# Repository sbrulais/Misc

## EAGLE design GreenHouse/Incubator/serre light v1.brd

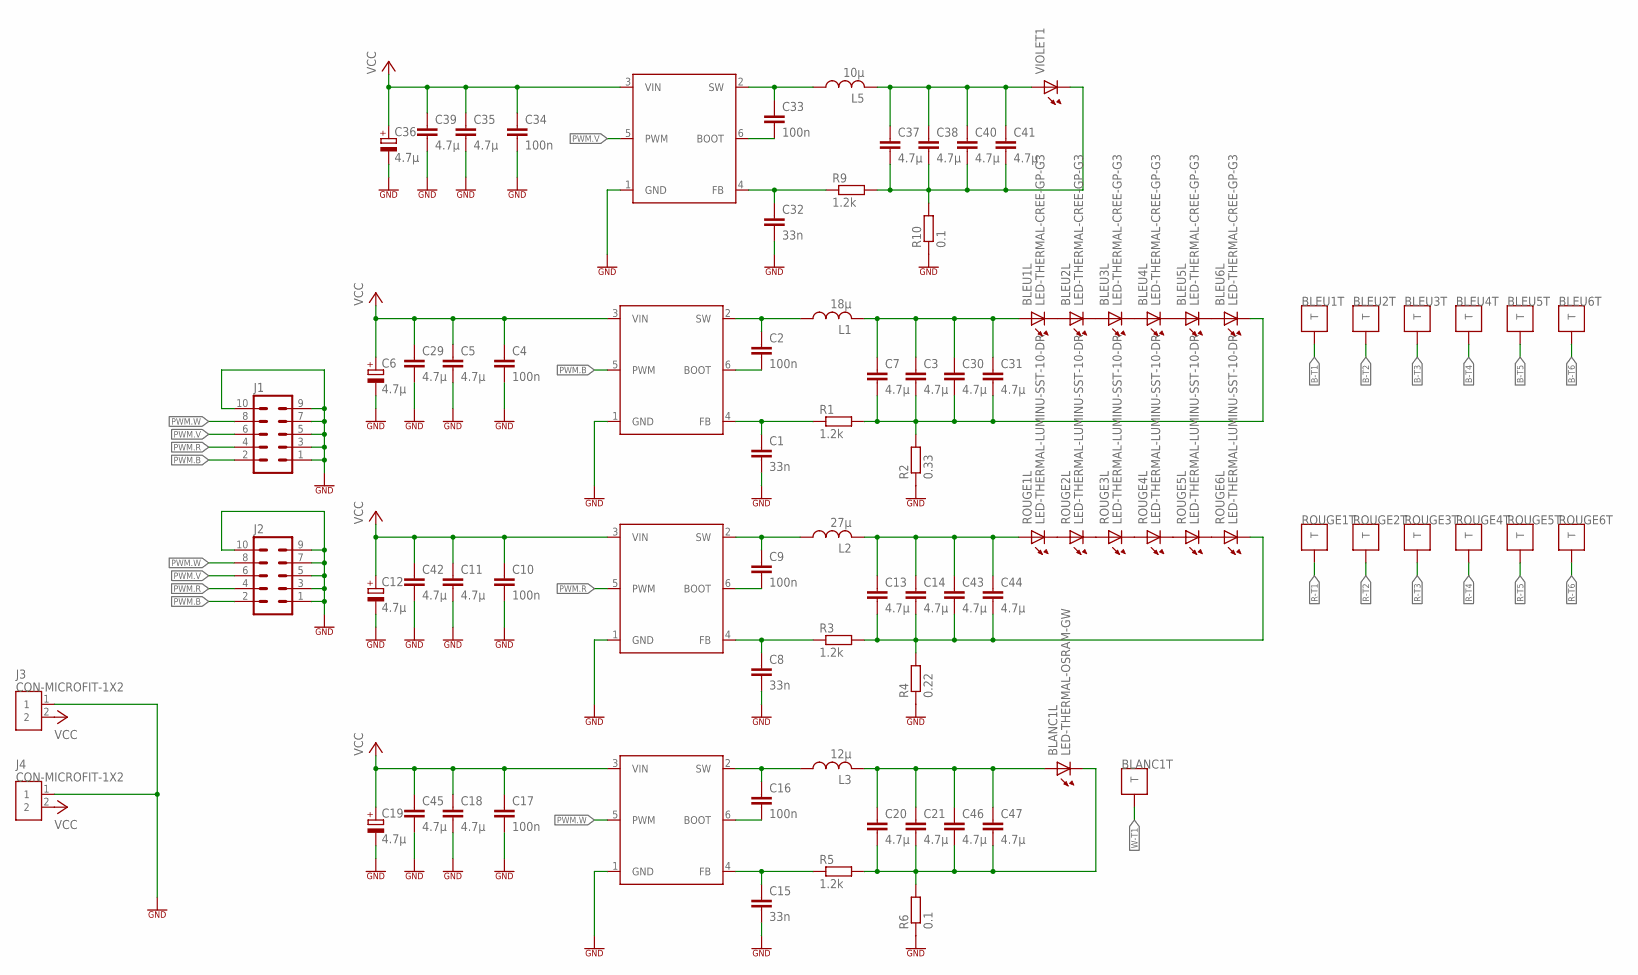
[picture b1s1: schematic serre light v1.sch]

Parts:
BLANC1: LED-THERMAL-OSRAM-GW; LED-OSRAM-GW
BLEU1, BLEU2, BLEU3, BLEU4, BLEU5, BLEU6: LED-THERMAL-CREE-GP-G3; LED-CREE-GP-G3
C1, C8, C15, C32: 33n; C0603
C2, C9, C16, C33: 100n; C0603
C3, C5, C7, C11, C13, C14, C18, C20, C21, C29, C30, C31, C35, C37, C38, C39, C40, C41, C42, C43, C44, C45, C46, C47: 4.7µ; C1210
C4, C10, C17, C34: 100n; C0805
C6, C12, C19, C36: 4.7µ; CAP-TANT-B
IC1, IC2, IC3, IC5: TPS54201; SOT23-6
J1, J2: ML10
J3, J4: CON-MICROFIT-1X2; MICROFIT-1X2
L1: 18µ; L-COILCRAFT-MSS1038; FARNELL 2288206
L2: 27µ; L-COILCRAFT-MSS1038; FARNELL 2288208
L3: 12µ; L-COILCRAFT-MSS1038; FARNELL 2288210
L5: 10µ; L-COILCRAFT-MSS1038; FARNELL 2288225
R1, R3, R5, R9: 1.2k; R0805
R2: 0.33; R1206; FARNELL 2328126
R4: 0.22; R1206; FARNELL 2824735
R6: 0.1; R1206; FARNELL 1100335
R10: 0.1; R1206; FARNELL 1099913
ROUGE1, ROUGE2, ROUGE3, ROUGE4, ROUGE5, ROUGE6: LED-THERMAL-LUMINU-SST-10-DR; LED-LUMINU-SST-10-DR
VIOLET1: LED-LUXEON-UV-U2

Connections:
B-T1: BLEU1.THERMAL (T)
B-T2: BLEU2.THERMAL (T)
B-T3: BLEU3.THERMAL (T)
B-T4: BLEU4.THERMAL (T)
B-T5: BLEU5.THERMAL (T)
B-T6: BLEU6.THERMAL (T)
GND: C1.2, C4.2, C5.2, C6.-, C8.2, C10.2, C11.2, C12.-, C15.2, C17.2, C18.2, C19.-, C29.2, C32.2, C34.2, C35.2, C36.-, C39.2, C42.2, C45.2, IC1.1 (GND), IC2.1 (GND), IC3.1 (GND), IC5.1 (GND), J1.1, J1.3, J1.5, J1.7, J1.9, J1.10, J2.1, J2.3, J2.5, J2.7, J2.9, J2.10, J3.1, J4.1, R2.1, R4.1, R6.1, R10.1
unnamed: BLEU2.C, BLEU3.A
unnamed: BLEU1.C, BLEU2.A
unnamed: BLEU3.C, BLEU4.A
unnamed: BLEU4.C, BLEU5.A
unnamed: ROUGE1.C, ROUGE2.A
unnamed: ROUGE2.C, ROUGE3.A
unnamed: ROUGE3.C, ROUGE4.A
unnamed: ROUGE5.C, ROUGE6.A
unnamed: ROUGE4.C, ROUGE5.A
unnamed: BLEU5.C, BLEU6.A
unnamed: C1.1, IC1.4 (FB), R1.1
unnamed: C2.1, IC1.2 (SW), L1.1
unnamed: C2.2, IC1.6 (BOOT)
unnamed: BLEU6.C, C3.2, C7.2, C30.2, C31.2, R1.2, R2.2
unnamed: C8.1, IC2.4 (FB), R3.1
unnamed: BLEU1.A, C3.1, C7.1, C30.1, C31.1, L1.2
unnamed: C9.1, IC2.2 (SW), L2.1
unnamed: C9.2, IC2.6 (BOOT)
unnamed: C13.2, C14.2, C43.2, C44.2, R3.2, R4.2, ROUGE6.C
unnamed: C13.1, C14.1, C43.1, C44.1, L2.2, ROUGE1.A
unnamed: C15.1, IC3.4 (FB), R5.1
unnamed: C16.1, IC3.2 (SW), L3.1
unnamed: C16.2, IC3.6 (BOOT)
unnamed: BLANC1.C, C20.2, C21.2, C46.2, C47.2, R5.2, R6.2
unnamed: BLANC1.A, C20.1, C21.1, C46.1, C47.1, L3.2
unnamed: C32.1, IC5.4 (FB), R9.1
unnamed: C33.1, IC5.2 (SW), L5.1
unnamed: C33.2, IC5.6 (BOOT)
unnamed: C37.2, C38.2, C40.2, C41.2, R9.2, R10.2, VIOLET1.C
unnamed: C37.1, C38.1, C40.1, C41.1, L5.2, VIOLET1.A
PWM.B: IC1.5 (PWM), J1.2, J2.2
PWM.R: IC2.5 (PWM), J1.4, J2.4
PWM.V: IC5.5 (PWM), J1.6, J2.6
PWM.W: IC3.5 (PWM), J1.8, J2.8
R-T1: ROUGE1.THERMAL (T)
R-T2: ROUGE2.THERMAL (T)
R-T3: ROUGE3.THERMAL (T)
R-T4: ROUGE4.THERMAL (T)
R-T5: ROUGE5.THERMAL (T)
R-T6: ROUGE6.THERMAL (T)
VCC: C4.1, C5.1, C6.+, C10.1, C11.1, C12.+, C17.1, C18.1, C19.+, C29.1, C34.1, C35.1, C36.+, C39.1, C42.1, C45.1, IC1.3 (VIN), IC2.3 (VIN), IC3.3 (VIN), IC5.3 (VIN), J3.2, J4.2
W-T1: BLANC1.THERMAL (T)

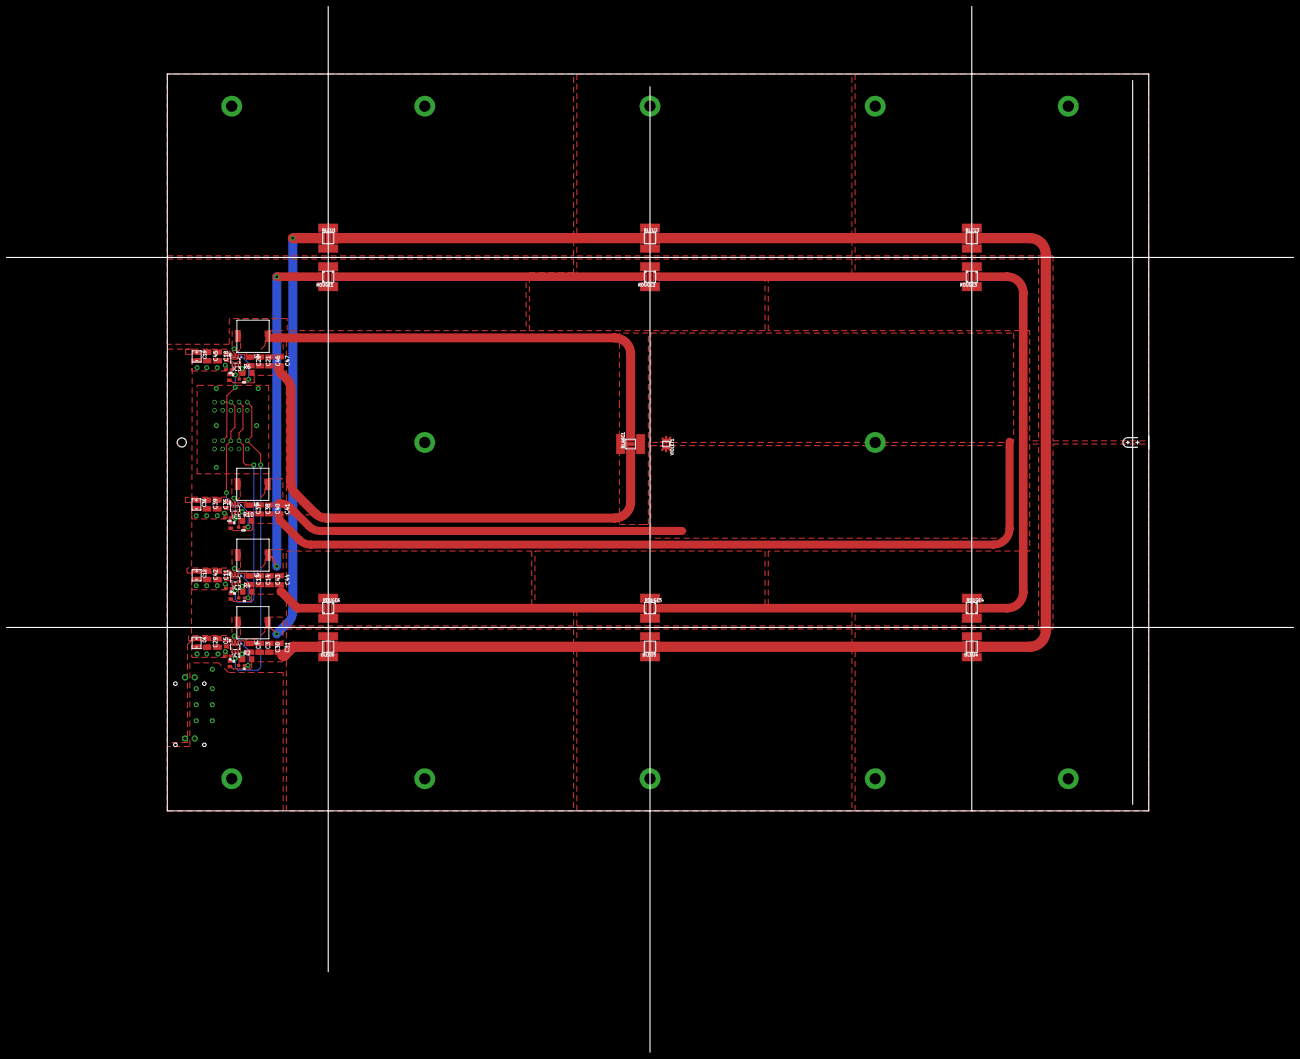
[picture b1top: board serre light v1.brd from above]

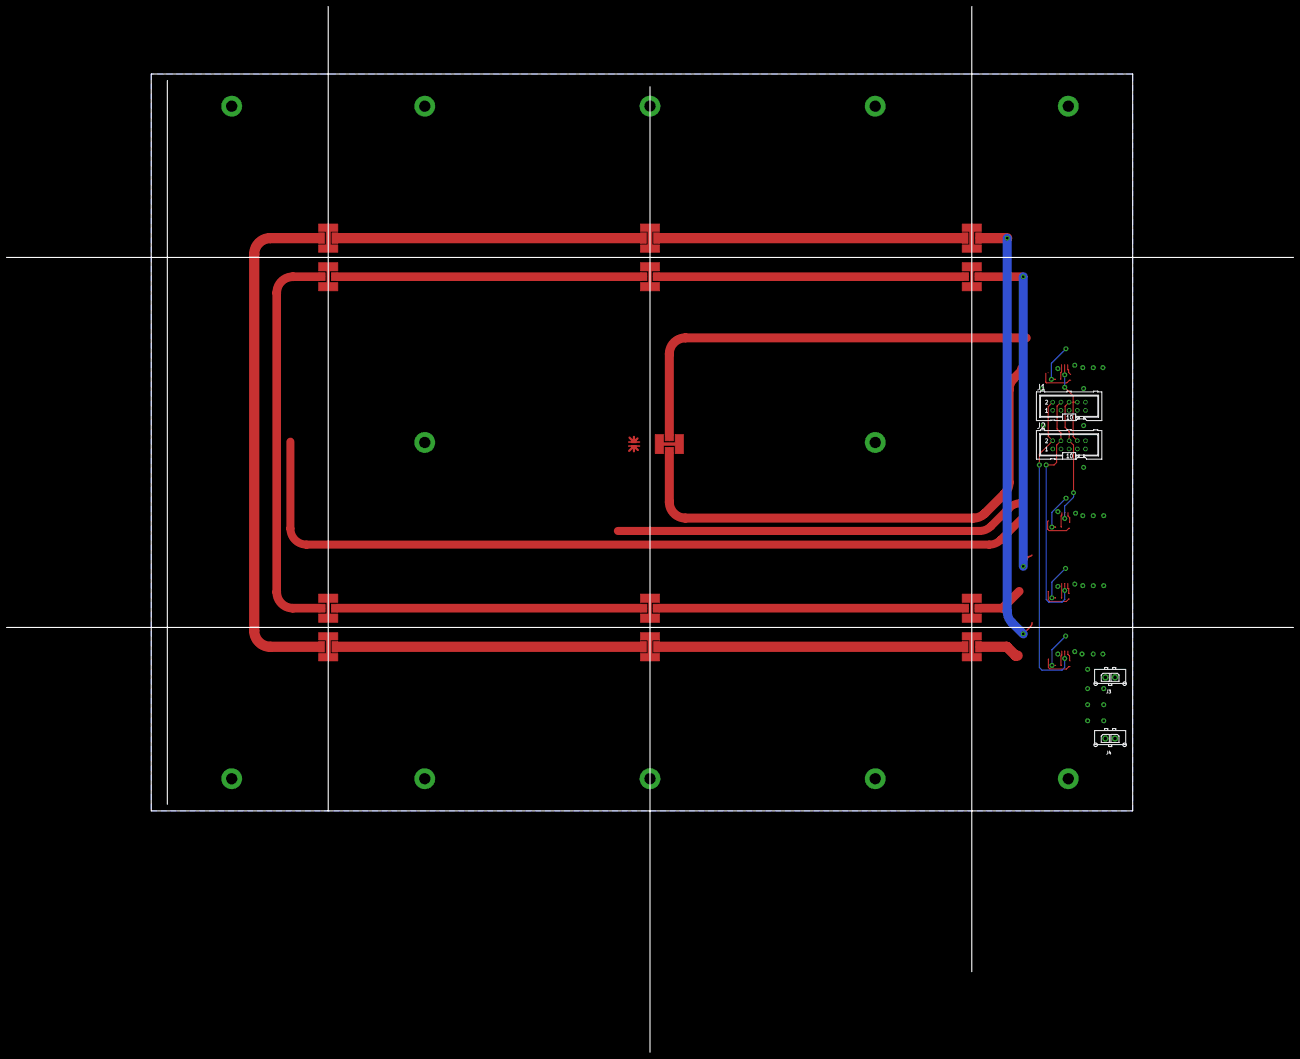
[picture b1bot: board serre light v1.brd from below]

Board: 2 copper layers, 400.0 x 325.0 mm, 74 parts (4 on the bottom side), 36 nets.

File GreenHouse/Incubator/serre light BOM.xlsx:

Cmd | Qty | Value | Device | Package | Parts | Description | FAB | FAB-REF | FARNELL | MF | MOUSER | MPN | OC_FARNELL | OC_NEWARK
ok | 1 |  | LED-LUXEON-UV-U2 | LED-LUXEON-UV-U2 | VIOLET1 | 0603 Rouge : Farnell 1685073
 | 2 |  | ML10 | ML10 | J1, J2 | HARTING |  |  |  |  |  |  | unknown | unknown
ok | 1 | 0.1 | R-EU_R1206 | R1206 | R10 | RESISTOR, European symbol |  |  | 1099913
ok | 1 | 0.1 | R-EU_R1206 | R1206 | R6 | RESISTOR, European symbol |  |  | 1100335
ok | 1 | 0.22 | R-EU_R1206 | R1206 | R4 | RESISTOR, European symbol |  |  | 2824735
ok | 1 | 0.33 | R-EU_R1206 | R1206 | R2 | RESISTOR, European symbol |  |  | 2328126
 | 4 | 1.2k | RR0805 | R0805 | R1, R3, R5, R9
 | 4 | 100n | CC0603 | C0603 | C2, C9, C16, C33
 | 4 | 100n | CC0805 | C0805 | C4, C10, C17, C34
ok | 1 | 10µ | L-MSS1038 | L-COILCRAFT-MSS1038 | L5 |  |  |  | 2288225
ok | 1 | 12µ | L-MSS1038 | L-COILCRAFT-MSS1038 | L3 |  |  |  | 2288210
ok | 1 | 18µ | L-MSS1038 | L-COILCRAFT-MSS1038 | L1 |  |  |  | 2288206
ok | 1 | 27µ | L-MSS1038 | L-COILCRAFT-MSS1038 | L2 |  |  |  | 2288208
 | 4 | 33n | CC0603 | C0603 | C1, C8, C15, C32
ok | 24 | 4.7µ | C-EUC1210 | C1210 | C3, C5, C7, C11, C13, C14, C18, C20, C21, C29, C30, C31, C35, C37, C38, C39, C4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 | CAPACITOR, European symbol
 | 4 | 4.7µ | CPOL-B | CAP-TANT-B | C6, C12, C19, C36
 | 2 | CON-MICROFIT-1X2 | CON-MICROFIT-1X2 | MICROFIT-1X2 | J3, J4 |  | MOLEX | 43650-0228 |  |  | 538-43650-0228
ok | 6 | LED-THERMAL-CREE-GP-G3 | LED-THERMAL-CREE-GP-G3 | LED-CREE-GP-G3 | BLEU1, BLEU2, BLEU3, BLEU4, BLEU5, BLEU6
ok | 6 | LED-THERMAL-LUMINU-SST-10-DR | LED-THERMAL-LUMINU-SST-10-DR | LED-LUMINU-SST-10-DR | ROUGE1, ROUGE2, ROUGE3, ROUGE4, ROUGE5, ROUGE6
ok | 1 | LED-THERMAL-OSRAM-GW | LED-THERMAL-OSRAM-GW | LED-OSRAM-GW | BLANC1
 | 4 | TPS54201 | TPS54201 | SOT23-6 | IC1, IC2, IC3, IC5

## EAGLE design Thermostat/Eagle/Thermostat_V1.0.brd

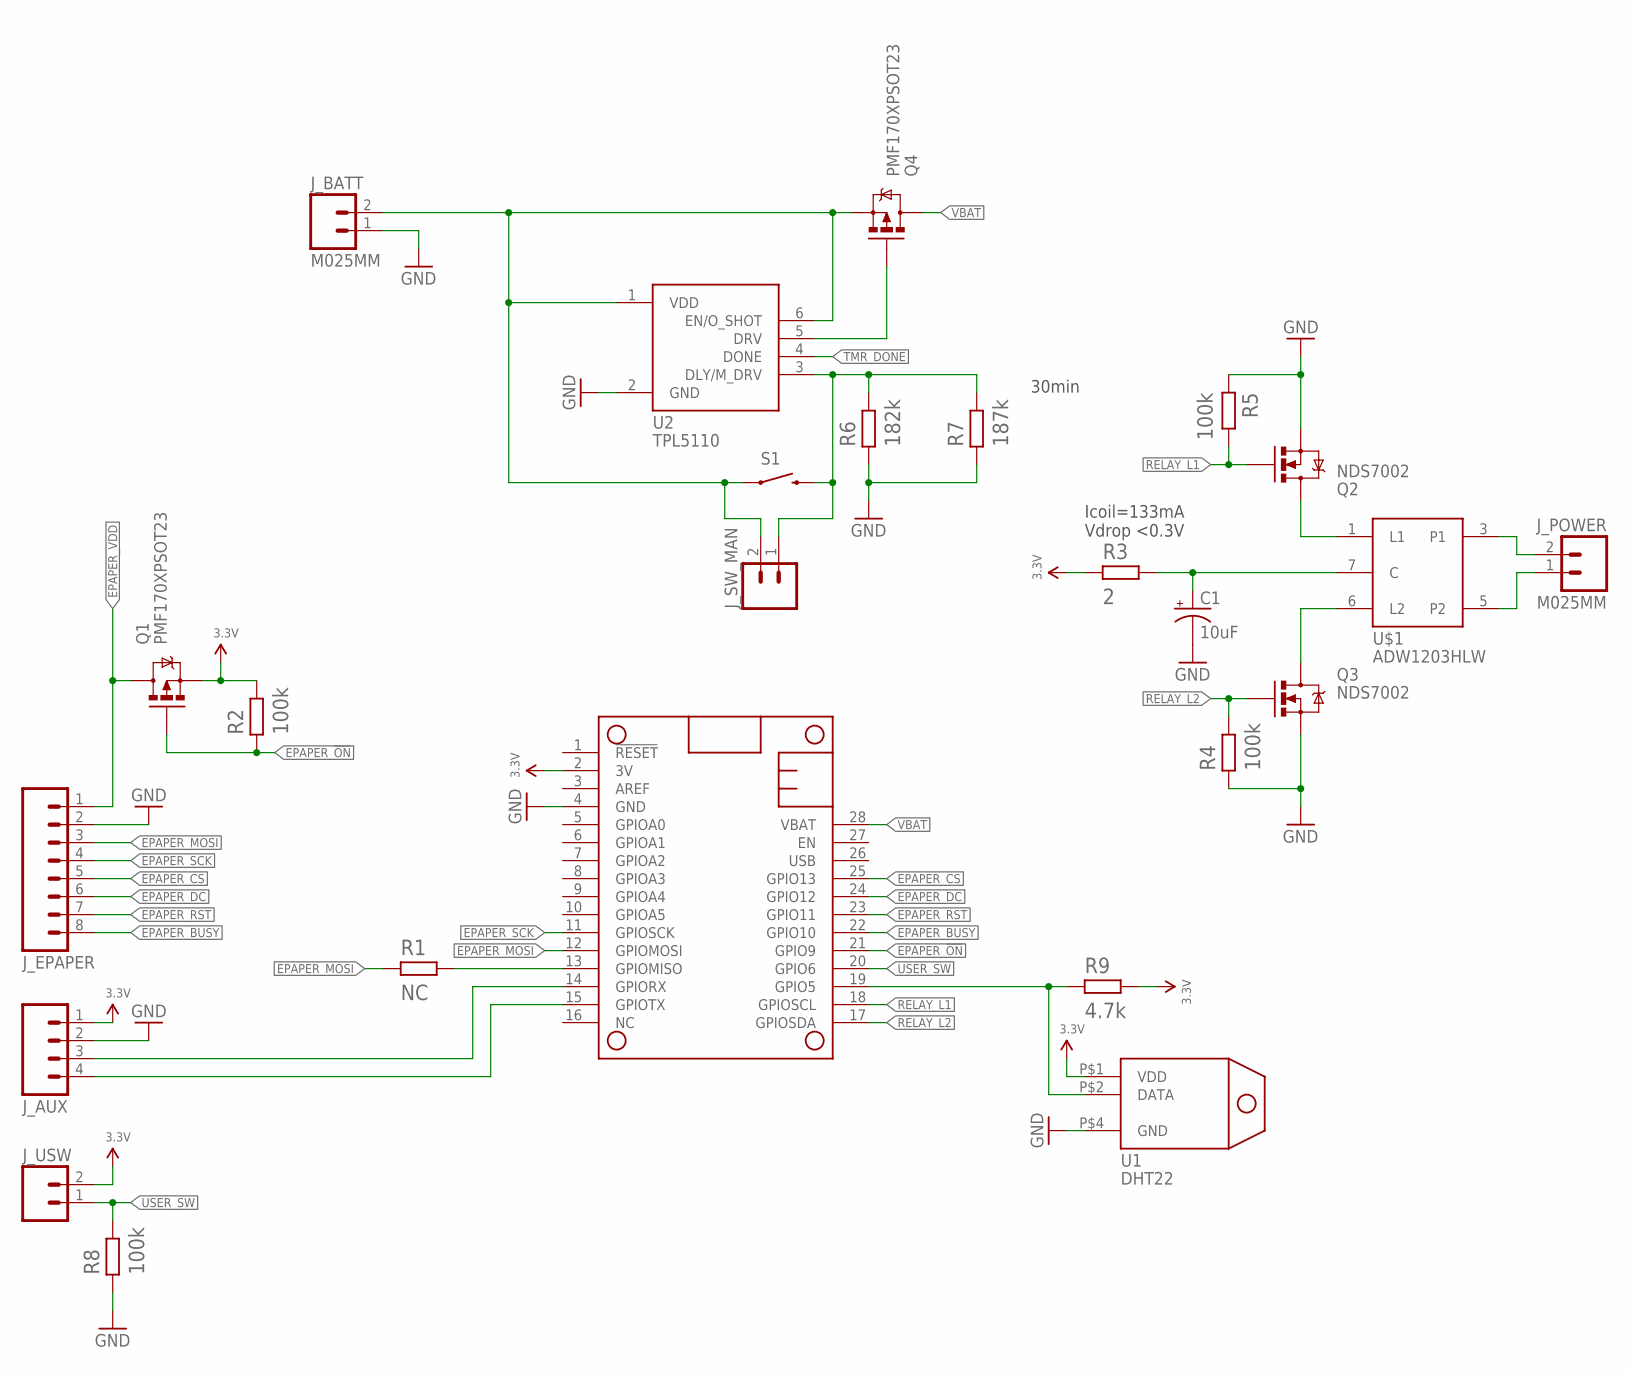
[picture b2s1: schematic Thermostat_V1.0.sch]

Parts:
C1: 10uF; CPOL-RADIAL-100UF-25V
J_AUX: M04LOCK; 1X04_LOCK
J_BATT: M025MM; SCREWTERMINAL-5MM-2
J_EPAPER: M081X08; 1X08
J_POWER: M025MM; SCREWTERMINAL-5MM-2
J_SW_MAN: M023.5MM-NO_SILK; SCREWTERMINAL-3.5MM-2-NS
J_USW: M023.5MM-NO_SILK; SCREWTERMINAL-3.5MM-2-NS
MS1: FEATHERWING
Q1, Q4: PMF170XPSOT23; SOT23
Q2, Q3: NDS7002; SOT23
R1: NC; R0805
R2, R4, R5, R8: 100k; R0805
R3: 2; R0805
R6: 182k; 1210
R7: 187k; 1210
R9: 4.7k; R0805
S1: SWITCH-MOMENTARY-2SMD-4; TACTILE_SWITCH_TALL
U1: DHT22
U2: TPL5110; SOT23-6
U$1: ADW1203HLW; DW_RELAY

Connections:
3.3V: J_AUX.1, J_USW.2, MS1.2 (3V), Q1.2 (S), R2.2, R3.1, R9.2, U1.P$1 (VDD)
EPAPER_!ON: MS1.21 (GPIO9), Q1.1 (G), R2.1
EPAPER_BUSY: J_EPAPER.8, MS1.22 (GPIO10)
EPAPER_CS: J_EPAPER.5, MS1.25 (GPIO13)
EPAPER_DC: J_EPAPER.6, MS1.24 (GPIO12)
EPAPER_MOSI: J_EPAPER.3, MS1.12 (GPIOMOSI), R1.1
EPAPER_RST: J_EPAPER.7, MS1.23 (GPIO11)
EPAPER_SCK: J_EPAPER.4, MS1.11 (GPIOSCK)
EPAPER_VDD: J_EPAPER.1, Q1.3 (D)
GND: C1.2 (-), J_AUX.2, J_BATT.1, J_EPAPER.2, MS1.4 (GND), Q2.2 (S), Q3.2 (S), R4.1, R5.1, R6.1, R7.1, R8.1, U1.P$4 (GND), U2.2 (GND)
unnamed: J_POWER.2, U$1.3 (P1)
unnamed: J_POWER.1, U$1.5 (P2)
unnamed: MS1.19 (GPIO5), R9.1, U1.P$2 (DATA)
unnamed: MS1.13 (GPIOMISO), R1.2
unnamed: C1.1 (+), R3.2, U$1.7 (C)
unnamed: Q2.3 (D), U$1.1 (L1)
unnamed: Q3.3 (D), U$1.6 (L2)
unnamed: Q4.1 (G), U2.5 (DRV)
unnamed: J_BATT.2, J_SW_MAN.2, Q4.2 (S), S1.A2 (1), U2.1 (VDD), U2.6 (EN/O_SHOT)
unnamed: J_SW_MAN.1, R6.2, R7.2, S1.B2 (2), U2.3 (DLY/M_DRV)
unnamed: J_AUX.3, MS1.14 (GPIORX)
unnamed: J_AUX.4, MS1.15 (GPIOTX)
RELAY_L1: MS1.18 (GPIOSCL), Q2.1 (G), R5.2
RELAY_L2: MS1.17 (GPIOSDA), Q3.1 (G), R4.2
TMR_DONE: U2.4 (DONE)
USER_SW: J_USW.1, MS1.20 (GPIO6), R8.2
VBAT: MS1.28 (VBAT), Q4.3 (D)

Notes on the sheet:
Icoil=133mA Vdrop <0.3V
30min

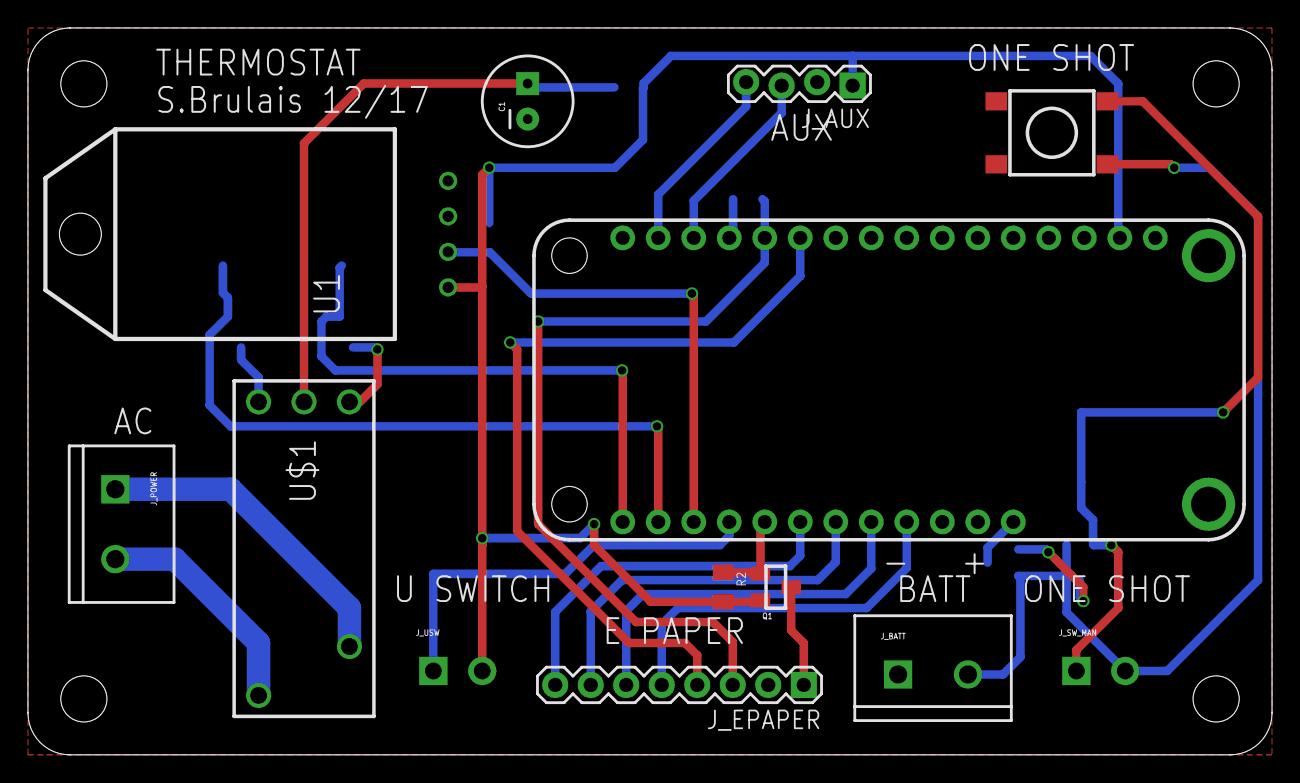
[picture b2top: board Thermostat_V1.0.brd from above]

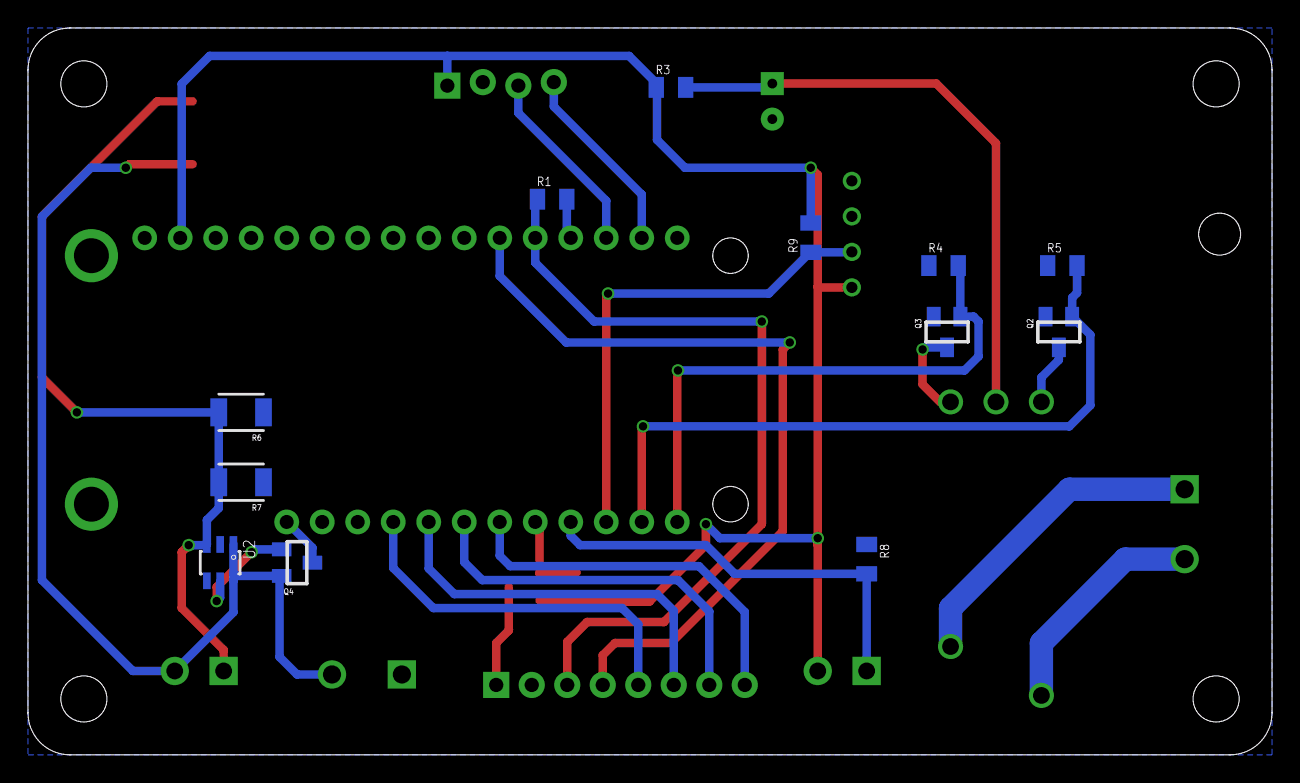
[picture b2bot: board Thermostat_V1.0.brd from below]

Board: 2 copper layers, 89.0 x 52.0 mm, 25 parts (12 on the bottom side), 26 nets.

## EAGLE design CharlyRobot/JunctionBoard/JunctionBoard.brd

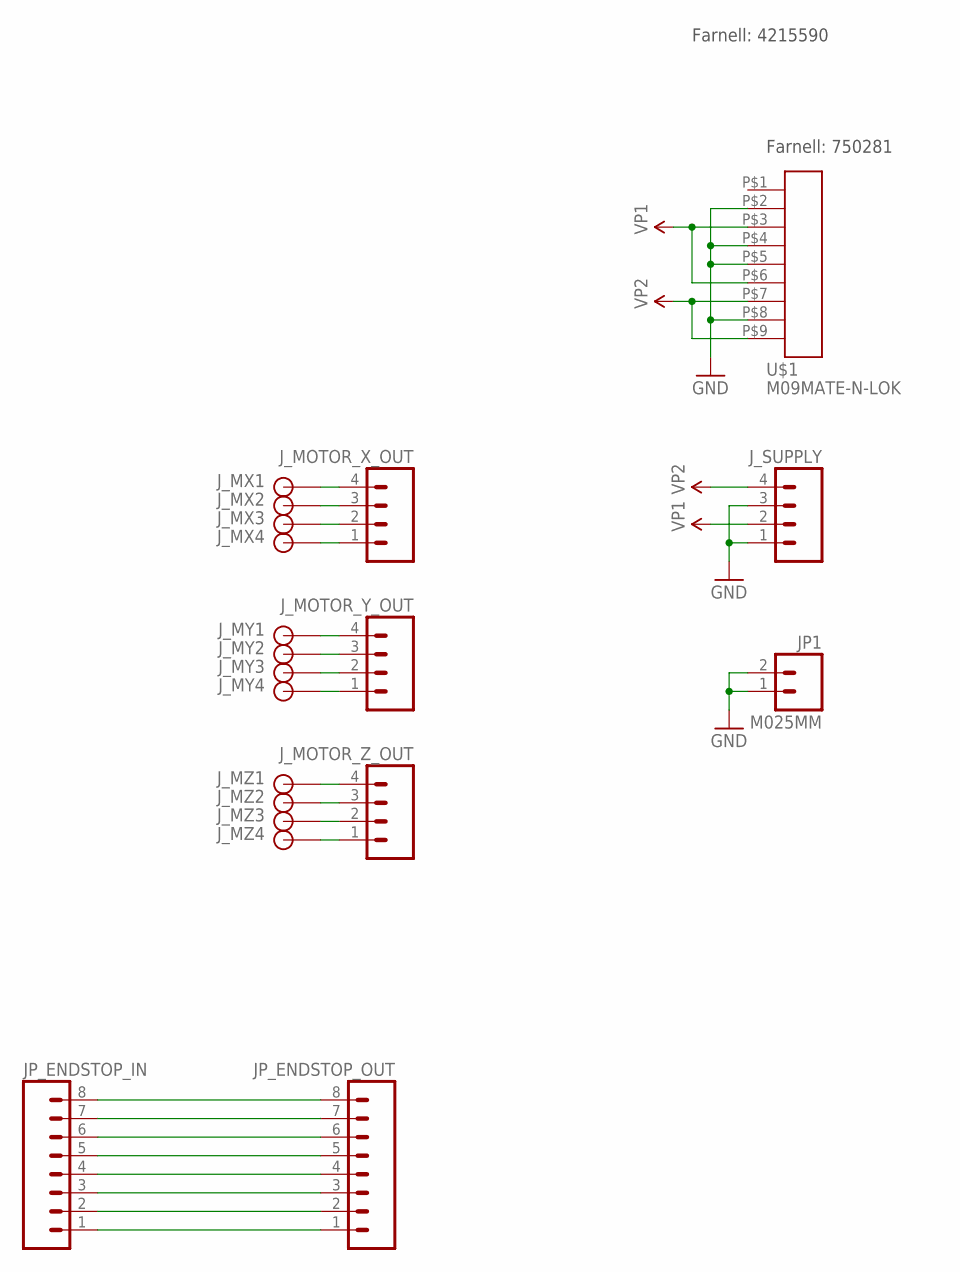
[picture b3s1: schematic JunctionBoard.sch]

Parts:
JP1: M025MM; SCREWTERMINAL-5MM-2
JP_ENDSTOP_IN: M083.5MM-8; SCREWTERMINAL-3.5MM-8
JP_ENDSTOP_OUT: M083.5MM-8; SCREWTERMINAL-3.5MM-8
J_MOTOR_X_OUT: M04SCREW5; SCREWTERMINAL-5MM-4
J_MOTOR_Y_OUT: M04SCREW5; SCREWTERMINAL-5MM-4
J_MOTOR_Z_OUT: M04SCREW5; SCREWTERMINAL-5MM-4
J_MX1, J_MX2, J_MX3, J_MX4: M01; FASTON-1
J_MY1, J_MY2, J_MY3, J_MY4: M01; FASTON-1
J_MZ1, J_MZ2, J_MZ3, J_MZ4: M01; FASTON-1
J_SUPPLY: M04SCREW5; SCREWTERMINAL-5MM-4
U$1: M09MATE-N-LOK; MATE-N-LOK-9

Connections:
GND: JP1.1, JP1.2, J_SUPPLY.1, J_SUPPLY.3, U$1.P$2, U$1.P$4, U$1.P$5, U$1.P$8
unnamed: J_MOTOR_X_OUT.4, J_MX1.P$1, J_MX1.P$2
unnamed: J_MOTOR_X_OUT.3, J_MX2.P$1, J_MX2.P$2
unnamed: J_MOTOR_X_OUT.2, J_MX3.P$1, J_MX3.P$2
unnamed: J_MOTOR_X_OUT.1, J_MX4.P$1, J_MX4.P$2
unnamed: J_MOTOR_Y_OUT.4, J_MY1.P$1, J_MY1.P$2
unnamed: J_MOTOR_Y_OUT.3, J_MY2.P$1, J_MY2.P$2
unnamed: J_MOTOR_Y_OUT.2, J_MY3.P$1, J_MY3.P$2
unnamed: J_MOTOR_Y_OUT.1, J_MY4.P$1, J_MY4.P$2
unnamed: J_MOTOR_Z_OUT.4, J_MZ1.P$1, J_MZ1.P$2
unnamed: J_MOTOR_Z_OUT.3, J_MZ2.P$1, J_MZ2.P$2
unnamed: J_MOTOR_Z_OUT.2, J_MZ3.P$1, J_MZ3.P$2
unnamed: J_MOTOR_Z_OUT.1, J_MZ4.P$1, J_MZ4.P$2
unnamed: JP_ENDSTOP_IN.1, JP_ENDSTOP_OUT.1
unnamed: JP_ENDSTOP_IN.2, JP_ENDSTOP_OUT.2
unnamed: JP_ENDSTOP_IN.3, JP_ENDSTOP_OUT.3
unnamed: JP_ENDSTOP_IN.4, JP_ENDSTOP_OUT.4
unnamed: JP_ENDSTOP_IN.5, JP_ENDSTOP_OUT.5
unnamed: JP_ENDSTOP_IN.6, JP_ENDSTOP_OUT.6
unnamed: JP_ENDSTOP_IN.7, JP_ENDSTOP_OUT.7
unnamed: JP_ENDSTOP_IN.8, JP_ENDSTOP_OUT.8
VP1: J_SUPPLY.2, U$1.P$3, U$1.P$6
VP2: J_SUPPLY.4, U$1.P$7, U$1.P$9

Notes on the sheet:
Farnell: 750281
Farnell: 4215590

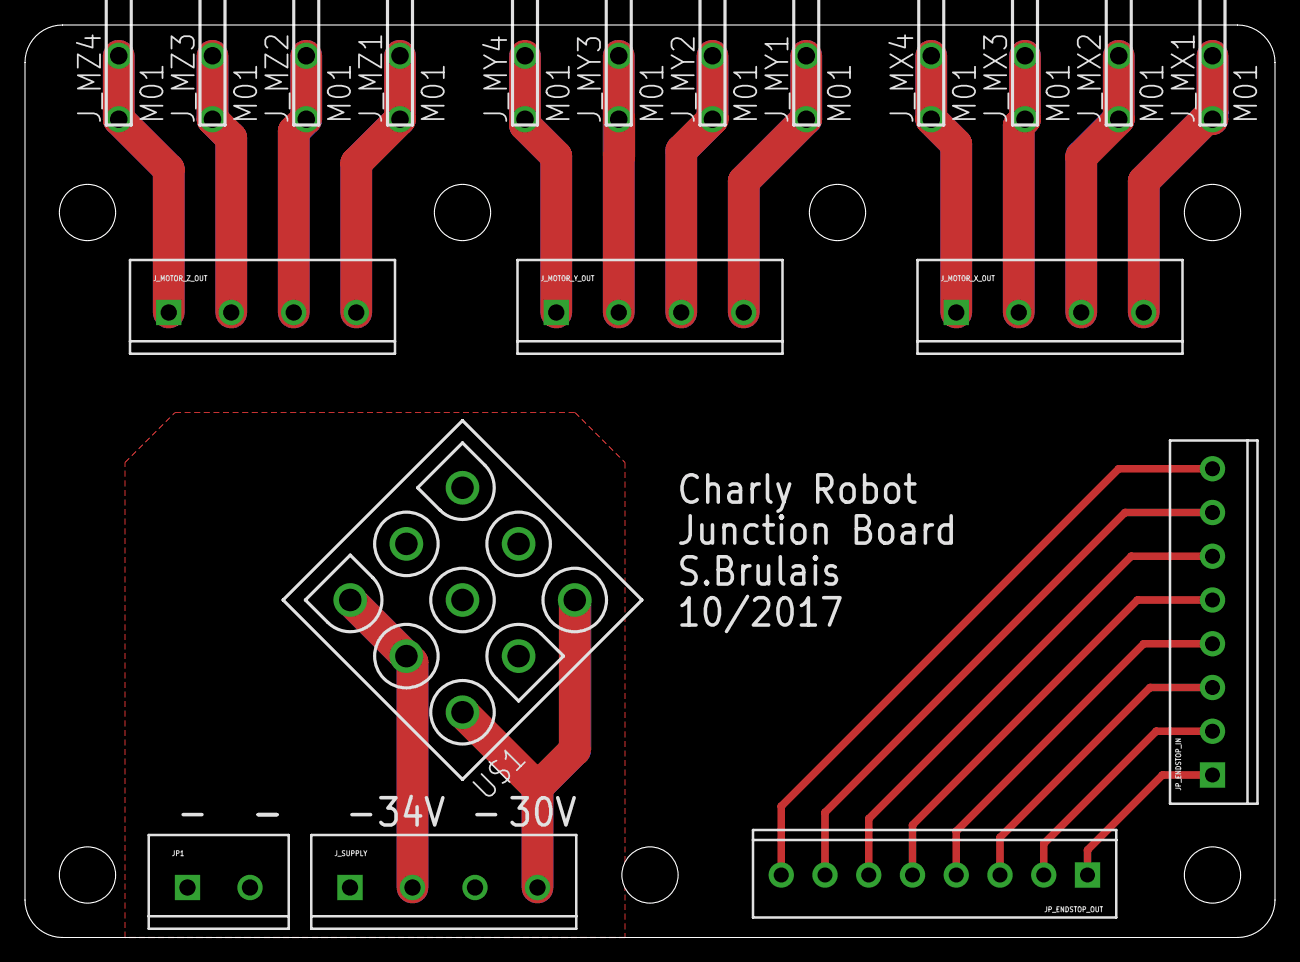
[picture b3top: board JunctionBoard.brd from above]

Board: 2 copper layers, 100.0 x 73.0 mm, 20 parts (0 on the bottom side), 23 nets.

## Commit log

2017-01-24 Galopin CNC first CAD commit
2017-01-24 Thermostat first test firmware
    TFT and relay working
2017-01-25 Galopin CNC gantry is wider
2017-01-25 Galopin CNC Y motor plate
2017-01-29 Minor updates before order
2017-02-27 Green house 2nd design
2017-02-27 Galopin CNC X motor plate update
2017-02-27 Thermostat basic test firmware
2017-03-05 Thermostat Casing CAD
2017-03-30 Galopin Z screw
2017-03-30 Green house bigger PC sheets
2017-03-30 Greenhouse is stiffer
2017-03-31 Green house minor updates
2017-05-05 Greenhouse assembly joint
2017-05-09 Green house new idea trial
2017-05-28 Greenhouse length adjusted
2017-05-29 Greenhouse rafter update
2017-05-30 Greenhouse updates
2017-05-30 Galopin CNC update
2017-06-01 Greenhouse final touch before cuts
2017-07-07 Galopin Milling parts
2017-07-08 T-nut charly
2017-07-30 SoilBlock, Car, CNC
2017-09-10 Wood Workshop walls
2017-09-11 Wood Workshop machines
2017-09-12 Seed bag
2017-09-21 G oak bed
2017-10-16 G oak bed updates
2017-10-18 Charly Robot junction board
2017-12-19 Charly junction board, house projects
2017-12-29 Seed bag drawings
2018-01-03 Gbed final lenght
2018-08-26 Greenhouse raised bed
2018-08-26 Gbed finished
2018-08-26 Maker gear M2 marlin's firmware working with graphical LCD
2018-10-29 Wheelchair draft
2018-10-29 Toy tractor steering wheel
2018-10-29 Wood workshop windows
2018-10-29 Thermostat arduino firmware
2019-01-09 Bar clamp first design
2019-01-09 Ender 3 Cura profile and parts
2019-01-09 Seed bag updates
2019-01-09 Thermostat casing updates
2019-01-12 Ender 3 cura profile
2019-01-12 RFLink software
2019-01-12 Sous pente kit
2019-01-12 Thermostat firmware wake up not working yet
2019-01-12 Ignore list
2019-01-12 Planer stand design
2019-01-12 Seed box pine prototype
2019-01-12 Toy Fan grip
2019-02-04 Thermostat bar clamp and M2 update
2019-02-14 Thermostat working but loose wifi connection
2019-02-14 Various house project updates
2019-02-24 Planner stand and miter saw
2019-03-02 Garden lattice
2019-03-18 Seed incubator and grainotheque doc
2019-03-21 Cat square stl
2019-03-21 Auto stash before merge of "master" and "origin/master"
2019-03-21 Serre light unused files
2019-03-21 Incubator CAM files
2019-03-26 Incubator working firmware
2019-03-28 Hache paille first drawing
2019-04-12 GreenHouse Incubator
2019-05-29 gutter and planner stand washers
2019-06-03 Gutter 1st update
2019-07-23 Various house projects
2019-07-23 GH and washer updates
2019-08-26 Wheelbarrow + fronde + disk sander
2019-09-05 Hache paille ameneur
2019-09-05 Milling wheelbarrow and disk sander
2019-10-25 WW Table saw stand
2019-11-02 Wheelbarrow plans
2019-11-06 G big bed
2019-11-14 Incubator fab + gbigbed redesign
2019-11-17 Bike square
2019-11-17 Wheels on table saw
2020-02-07 Cheville & bbed drawings
2020-02-28 seedling cart
2020-03-05 Marco Pilot initial commit
2020-03-05 Serre light v2 debug updates
2020-07-29 Pieces fauteuil
2020-07-29 Greenhouse gutter remake
2020-07-29 Seed cleaner
2020-07-29 Chicken house
2020-07-29 Brushcutter toy
2020-07-29 Bandsaw stand
2020-07-29 KW router table
2020-07-29 Some shopvac adapters
2020-09-18 Toy: crane first version
2020-09-18 Wrench for tank, WIP
2020-09-18 Toy night light WIP
2020-09-18 Maker gear Marlin V2,config todo
2022-12-13 Bump qs
    Bumps [qs](https://github.com/ljharb/qs) from 6.5.2 to 6.5.3.
    - [Release notes](https://github.com/ljharb/qs/releases)
    - [Changelog](https://github.com/ljharb/qs/blob/main/CHANGELOG.md)
    - [Commits](https://github.com/ljharb/qs/compare/v6.5.2...v6.5.3)
    ---
    updated-dependencies:
2023-10-16 Macro pilot last comit
2023-10-16 3D4C flex demo
2023-10-16 Various fishing parts
2023-10-16 Ender 3 updates
2023-10-16 Composting toilet design
2023-10-17 Soil block maker
2023-10-17 Beer Cart for Robby
2023-10-17 Chicken House actually done
2023-10-17 Cool coat hanger redesign
2023-10-17 Laser cutter air extract
2023-10-17 3D printed mouse trap
2023-10-17 Bedroom shelves
2023-10-17 kid's step stool
2023-10-17 Step_stool assy file
2023-10-17 Tango bed done
2025-07-22 Bump form-data and vscode
    Removes [form-data](https://github.com/form-data/form-data). It's no longer used after updating ancestor dependency [vscode](https://github.com/Microsoft/vscode-extension-vscode). These dependencies 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
    Removes `form-data`
    Updates `vscode` from 1.1.17 to 1.1.37
    - [Commits](https://github.com/Microsoft/vscode-extension-vscode/compare/1.1.17...v1.1.37)
    ---
    updated-dependencies:
2025-11-18 Bump js-yaml
    Bumps [js-yaml](https://github.com/nodeca/js-yaml) from 3.12.0 to 3.14.2.
    - [Changelog](https://github.com/nodeca/js-yaml/blob/master/CHANGELOG.md)
    - [Commits](https://github.com/nodeca/js-yaml/compare/3.12.0...3.14.2)
    ---
    updated-dependencies:
    - dependency-name: js-yaml
2026-01-01 Bump qs and vscode
    Removes [qs](https://github.com/ljharb/qs). It's no longer used after updating ancestor dependency [vscode](https://github.com/Microsoft/vscode-extension-vscode). These dependencies need to be update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
    Removes `qs`
    Updates `vscode` from 1.1.17 to 1.1.37
    - [Commits](https://github.com/Microsoft/vscode-extension-vscode/compare/1.1.17...v1.1.37)
    ---
    updated-dependencies:
2026-01-17 Bump tar and vscode
    Removes [tar](https://github.com/isaacs/node-tar). It's no longer used after updating ancestor dependency [vscode](https://github.com/Microsoft/vscode-extension-vscode). These dependencies need to be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
    Removes `tar`
    Updates `vscode` from 1.1.17 to 1.1.37
    - [Commits](https://github.com/Microsoft/vscode-extension-vscode/compare/1.1.17...v1.1.37)
    ---
    updated-dependencies:

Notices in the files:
parts and their libraries:
SparkFun-Connectors: Licensing: Creative Commons ShareAlike 4.0 International - https://creativecommons.org/licenses/by-sa/4.0
